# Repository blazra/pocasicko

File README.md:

# Počasíčko

LoRa node with e-paper display and BME680
- Murata CMWX1ZZABZ-091: Semtech SX1276 + STM32L072
- Bosch Sensortec BME680 measures pressure, humidity, temperature and Volatile Organic Compounds (VOC)
- Waveshare 4.2" EPD 400x300
- Powered from three AA batteries

Revision 1 known issues:
- Missing divider for battery voltage monitoring
- Unable to wake-up from standby using BUTTON_A (WKUP1), because pull-ups are disconnected in standby mode

[Schematic](./pcb/revision_1/pocasicko-schematic.pdf)

---
Počasíčko means little weather in Czech

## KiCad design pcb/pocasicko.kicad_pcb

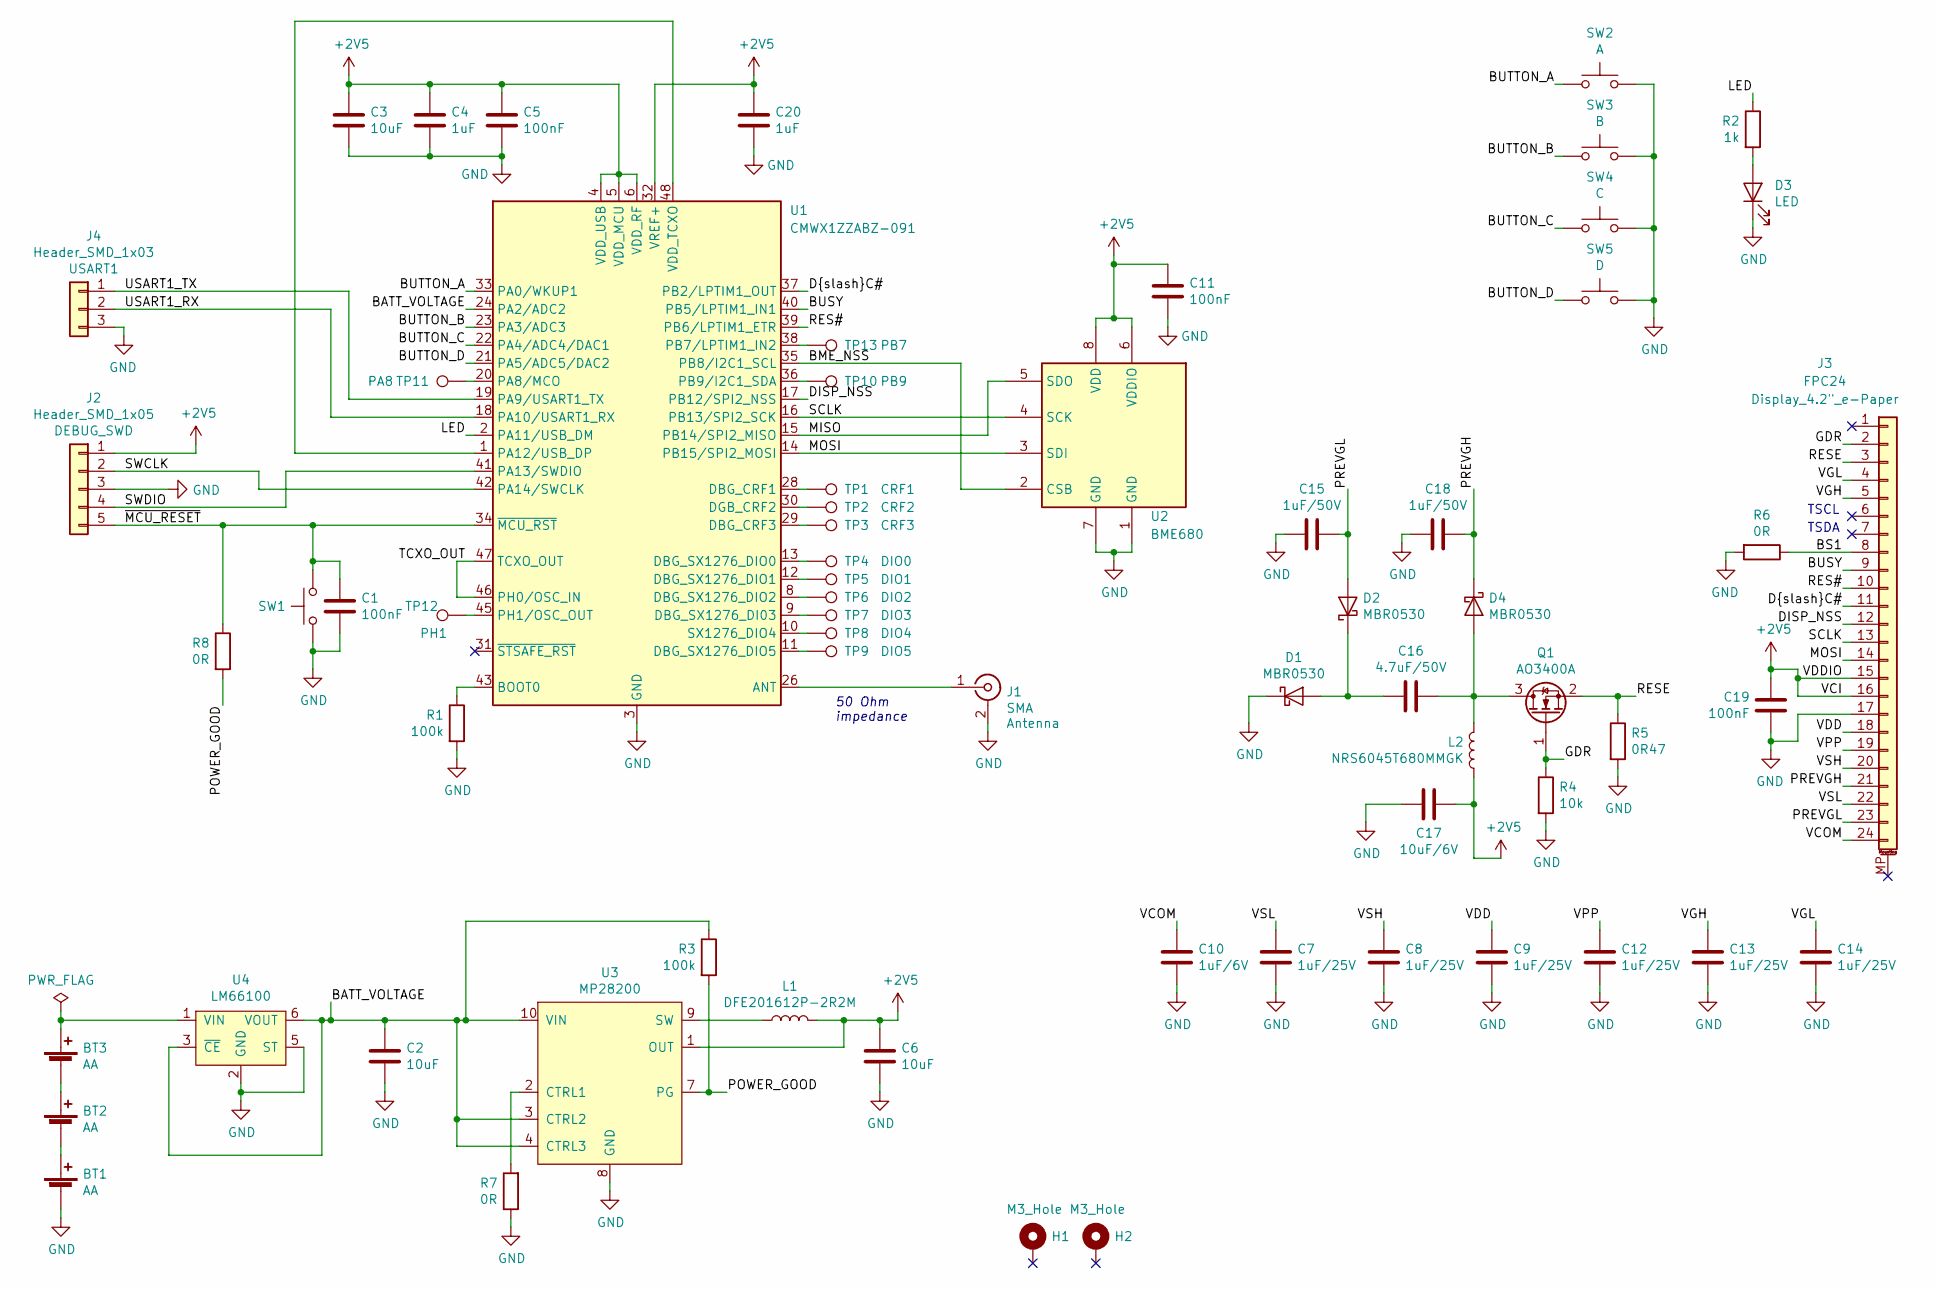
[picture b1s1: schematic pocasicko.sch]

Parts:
BT1, BT2, BT3: AA; BatteryHolder_Keystone_53_1xAA
C1, C5, C11, C19: 100nF; C_0805_2012Metric
C2, C3, C6: 10uF; C_0805_2012Metric
C4, C20: 1uF; C_0805_2012Metric
C7, C8, C9, C12, C13, C14: 1uF/25V; C_0805_2012Metric
C10: 1uF/6V; C_0805_2012Metric
C15, C18: 1uF/50V; C_1206_3216Metric
C16: 4.7uF/50V; C_1206_3216Metric
C17: 10uF/6V; C_0805_2012Metric
D1, D2, D4: MBR0530; D_SOD-123
D3: LED; LED_0805_2012Metric_Castellated
H1, H2: M3_Hole; MountingHole_3.2mm_M3_DIN965_Pad
J1: SMA; SMA_Samtec_SMA-J-P-H-ST-EM1_EdgeMount
J2: Header_SMD_1x05; PinHeader_1x05_P2.54mm_Vertical_SMD_Pin1Left
J3: FPC24; Waveshare_EPD_4.2_Amphenol_SFV24R-4STBE1HLF
J4: Header_SMD_1x03; PinHeader_1x03_P2.54mm_Vertical_SMD_Pin1Left
L1: DFE201612P-2R2M; L_0806_2016Metric
L2: NRS6045T680MMGK; L_Taiyo-Yuden_NR-60xx
Q1: AO3400A; SOT-23
R1, R3: 100k; R_0805_2012Metric
R2: 1k; R_0805_2012Metric
R4: 10k; R_0805_2012Metric
R5: 0R47; R_1206_3216Metric
R6, R7, R8: 0R; R_0805_2012Metric
SW1: RESET; SW_Push_1P1T_NO_6x6mm_H9.5mm
SW2: A; SW_SPST_EVQQ2
SW3: B; SW_SPST_EVQQ2
SW4: C; SW_SPST_EVQQ2
SW5: D; SW_SPST_EVQQ2
TP1: CRF1; TestPoint_Pad_D1.0mm
TP2: CRF2; TestPoint_Pad_D1.0mm
TP3: CRF3; TestPoint_Pad_D1.0mm
TP4: DIO0; TestPoint_Pad_D1.0mm
TP5: DIO1; TestPoint_Pad_D1.0mm
TP6: DIO2; TestPoint_Pad_D1.0mm
TP7: DIO3; TestPoint_Pad_D1.0mm
TP8: DIO4; TestPoint_Pad_D1.0mm
TP9: DIO5; TestPoint_Pad_D1.0mm
TP10: PB9; TestPoint_Pad_D1.0mm
TP11: PA8; TestPoint_Pad_D1.0mm
TP12: PH1; TestPoint_Pad_D1.0mm
TP13: PB7; TestPoint_Pad_D1.0mm
U1: CMWX1ZZABZ-091; CMWX1ZZABZ
U2: BME680; Bosch_LGA-8_3x3mm_P0.8mm_ClockwisePinNumbering
U3: MP28200; QFN-12_2x2_Pitch0.4mm
U4: LM66100; SOT-363_SC-70-6

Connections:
+2V5: C3.2, C4.2, C5.2, C6.2, C11.2, C17.2, C19.2, C20.2, J2.1, J3.15, J3.16, L1.2, L2.1, U1.4 (VDD_USB), U1.5 (VDD_MCU), U1.6 (VDD_RF), U1.32 (VREF+), U2.6 (VDDIO), U2.8 (VDD), U3.1 (OUT)
/BATT_VOLTAGE: C2.2, R3.1, U1.24 (PA2/ADC2), U3.3 (CTRL2), U3.4 (CTRL3), U3.10 (VIN), U4.3 (~CE), U4.6 (VOUT)
/BME_NSS: U1.35 (PB8/I2C1_SCL), U2.2 (CSB)
/BS1: J3.8, R6.1
/BUSY: J3.9, U1.40 (PB5/LPTIM1_IN1)
/BUTTON_A: SW2.1, U1.33 (PA0/WKUP1)
/BUTTON_B: SW3.1, U1.23 (PA3/ADC3)
/BUTTON_C: SW4.1, U1.22 (PA4/ADC4/DAC1)
/BUTTON_D: SW5.1, U1.21 (PA5/ADC5/DAC2)
/DISP_NSS: J3.12, U1.17 (PB12/SPI2_NSS)
/D/C#: J3.11, U1.37 (PB2/LPTIM1_OUT)
/GDR: J3.2, Q1.1 (G), R4.1
/LED: R2.1, U1.2 (PA11/USB_DM)
/MISO: U1.15 (PB14/SPI2_MISO), U2.5 (SDO)
/MOSI: J3.14, U1.14 (PB15/SPI2_MOSI), U2.3 (SDI)
/POWER_GOOD: R3.2, R8.2, U3.7 (PG)
/PREVGH: C18.1, D4.1 (K), J3.21
/PREVGL: C15.1, D2.2 (A), J3.23
/RES#: J3.10, U1.39 (PB6/LPTIM1_ETR)
/RESE: J3.3, Q1.2 (S), R5.1
/SCLK: J3.13, U1.16 (PB13/SPI2_SCK), U2.4 (SCK)
/SWCLK: J2.2, U1.42 (PA14/SWCLK)
/SWDIO: J2.4, U1.41 (PA13/SWDIO)
/TCXO_OUT: U1.46 (PH0/OSC_IN), U1.47 (TCXO_OUT)
/USART1_RX: J4.2, U1.18 (PA10/USART1_RX)
/USART1_TX: J4.1, U1.19 (PA9/USART1_TX)
/VCOM: C10.2, J3.24
/VDD: C9.2, J3.18
/VGH: C13.2, J3.5
/VGL: C14.2, J3.4
/VPP: C12.2, J3.19
/VSH: C8.2, J3.20
/VSL: C7.2, J3.22
/~MCU_RESET: C1.1, J2.5, R8.1, SW1.2, U1.34 (~MCU_RST)
GND: BT1.2 (-), C1.2, C2.1, C3.1, C4.1, C5.1, C6.1, C7.1, C8.1, C9.1, C10.1, C11.1, C12.1, C13.1, C14.1, C15.2, C17.1, C18.2, C19.1, C20.1, D1.1 (K), D3.1 (K), J1.2 (Ext), J2.3, J3.17, J4.3, R1.2, R4.2, R5.2, R6.2, R7.1, SW1.1, SW2.2, SW3.2, SW4.2, SW5.2, U1.3 (GND), U1.7 (GND), U1.25 (GND), U1.27 (GND), U1.44 (GND), U1.49 (GND), U1.50 (GND), U1.51 (GND), U1.52 (GND), U1.53 (GND), U1.54 (GND), U1.55 (GND), U1.56 (GND), U1.57 (GND), U2.1 (GND), U2.7 (GND), U3.5 (TP), U3.6 (TP), U3.8 (GND), U4.2 (GND), U4.5 (ST)
unnamed: BT1.1 (+), BT2.2 (-)
unnamed: BT2.1 (+), BT3.2 (-)
unnamed: BT3.1 (+), U4.1 (VIN)
unnamed: C16.1, D4.2 (A), L2.2, Q1.3 (D)
unnamed: C16.2, D1.2 (A), D2.1 (K)
unnamed: D3.2 (A), R2.2
unnamed: J1.1 (In), U1.26 (ANT)
unnamed: L1.1, U3.9 (SW)
unnamed: R1.1, U1.43 (BOOT0)
unnamed: R7.2, U3.2 (CTRL1)
unnamed: TP1.1, U1.28 (DBG_CRF1)
unnamed: TP2.1, U1.30 (DGB_CRF2)
unnamed: TP3.1, U1.29 (DBG_CRF3)
unnamed: TP4.1, U1.13 (DBG_SX1276_DIO0)
unnamed: TP5.1, U1.12 (DBG_SX1276_DIO1)
unnamed: TP6.1, U1.8 (DBG_SX1276_DIO2)
unnamed: TP7.1, U1.9 (DBG_SX1276_DI03)
unnamed: TP8.1, U1.10 (SX1276_DIO4)
unnamed: TP9.1, U1.11 (DBG_SX1276_DIO5)
unnamed: TP10.1, U1.36 (PB9/I2C1_SDA)
unnamed: TP11.1, U1.20 (PA8/MCO)
unnamed: TP12.1, U1.45 (PH1/OSC_OUT)
unnamed: TP13.1, U1.38 (PB7/LPTIM1_IN2)
unnamed: U1.1 (PA12/USB_DP), U1.48 (VDD_TCXO)

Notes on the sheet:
50 Ohm impedance
TSCL
TSDA

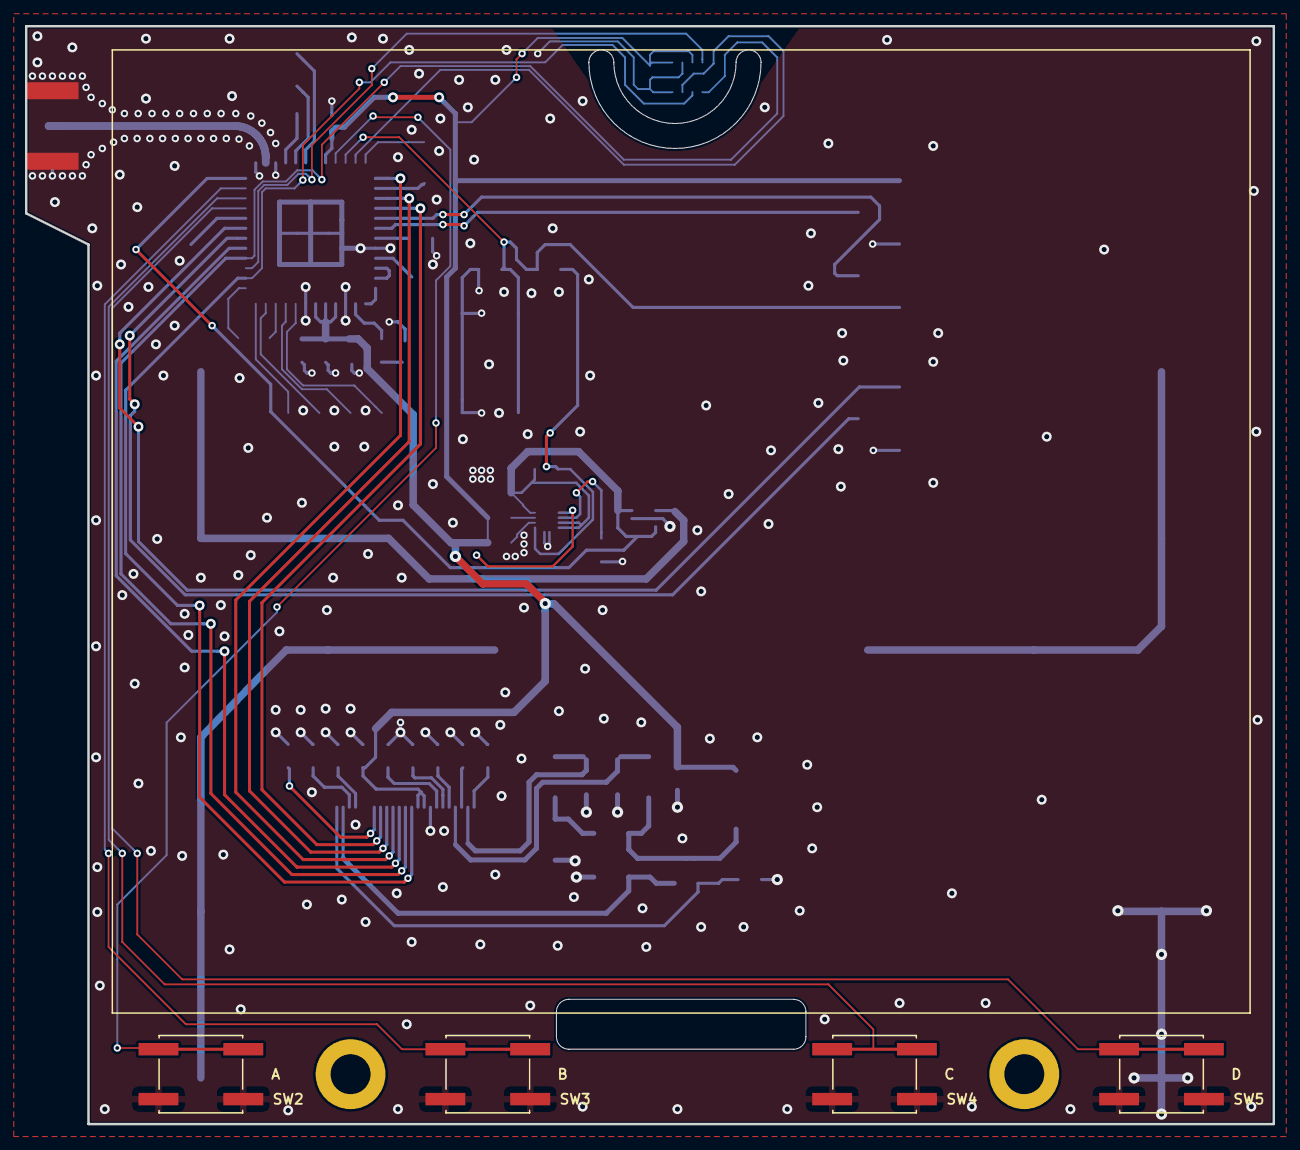
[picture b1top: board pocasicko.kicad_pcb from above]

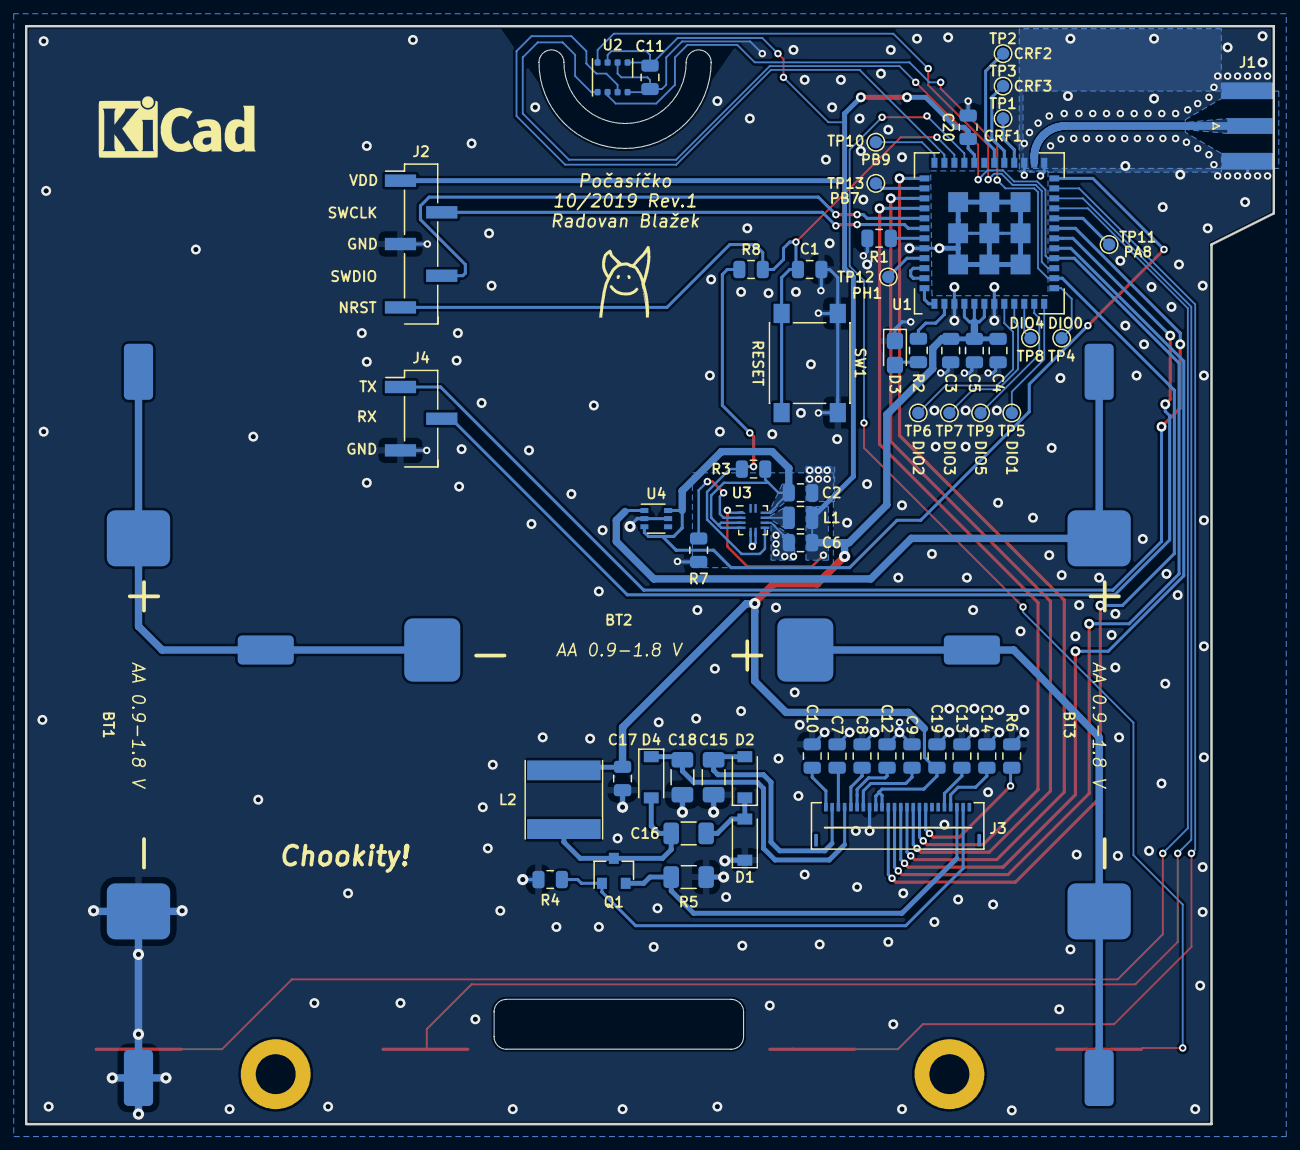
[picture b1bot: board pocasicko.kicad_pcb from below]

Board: 2 copper layers, 100.0 x 88.0 mm, 66 parts (60 on the bottom side), 59 nets.

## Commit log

2019-10-22 Finish schematic and large component placement
    All components chosen and placed on the PCB before routing and
    schematic probably mostly finished.
2019-10-22 Add license
2019-10-22 Update README to reflect current design decisions
2019-10-27 Routing progress
2019-10-27 Rotate LoRa module
2019-10-27 Rotate the center cell diagonally
2019-10-29 Finished routing
2019-10-29 Exchange SMA and add groundplane to the back layer
2019-10-30 Change BME interface from I2C to SPI
2019-10-30 Enlarge the EPD flat flex hole
2019-11-01 Exchanged FPC connector. This is the Rev. 1.
2019-11-01 Add revision 1 gerbers
2019-11-02 Add schematic pdf
2019-11-02 Rename schematic file
2019-11-02 Set footprints to use 3D models from ./packages3d/
2019-11-02 Add revision 1 pcb renders
